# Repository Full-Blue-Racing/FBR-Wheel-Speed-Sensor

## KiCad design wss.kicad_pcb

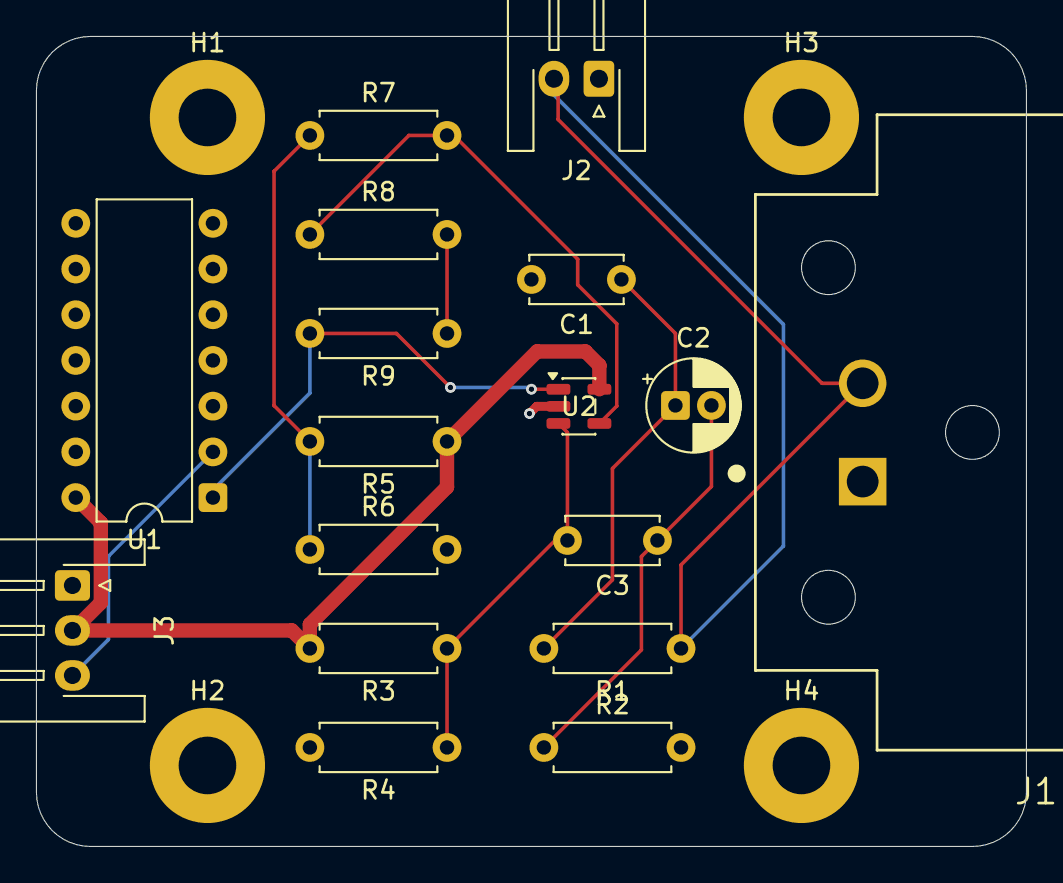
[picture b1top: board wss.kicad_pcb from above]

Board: 2 copper layers, 55.0 x 45.0 mm, 21 parts (0 on the bottom side), 11 nets.

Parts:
C1: 80n; C_Disc_D5.0mm_W2.5mm_P5.00mm
C2: 10u; CP_Radial_D5.0mm_P2.00mm
C3: 1u; C_Disc_D5.0mm_W2.5mm_P5.00mm
H1, H2, H3, H4: MountingHole_Pad; MountingHole_3.2mm_M3_Pad
J1: Conn_01x02; TE_DT13-2P
J2: Conn_01x02; JST_XH_S2B-XH-A-1_1x02_P2.50mm_Horizontal
J3: Conn_01x03; JST_XH_S3B-XH-A-1_1x03_P2.50mm_Horizontal
R1: 3.9k; R_Axial_DIN0207_L6.3mm_D2.5mm_P7.62mm_Horizontal
R2: 10k; R_Axial_DIN0207_L6.3mm_D2.5mm_P7.62mm_Horizontal
R3, R4, R5, R6: 150k; R_Axial_DIN0207_L6.3mm_D2.5mm_P7.62mm_Horizontal
R7: 5.6k; R_Axial_DIN0207_L6.3mm_D2.5mm_P7.62mm_Horizontal
R8: 5.6M; R_Axial_DIN0207_L6.3mm_D2.5mm_P7.62mm_Horizontal
R9: 0; R_Axial_DIN0207_L6.3mm_D2.5mm_P7.62mm_Horizontal
U1: 74HC14; DIP-14_W7.62mm
U2: TLV9061xDBV; SOT-23-5

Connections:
+3V3: J3.2, R3.2, R5.1, U1.14 (VCC), U2.5 (V+)
/Signal2: J1.2, J2.2, R1.1
/Signal_Output: J3.3, U1.2
GND: C1.2, H1.1, H2.1, H3.1, H4.1, J1.1, J2.1, J3.1, R2.2, R4.2, R6.2, U1.3, U1.4, U1.5, U1.6, U1.7 (GND), U1.8, U1.9, U1.10, U1.11, U1.12, U1.13, U2.2 (V-)
unnamed: C1.1, C2.1, R1.2
unnamed: C2.2, C3.1, R2.1
unnamed: R5.2, R6.1, R7.1
unnamed: R8.2, R9.1
unnamed: R9.2, U1.1, U2.1
unnamed: C3.2, R3.1, R4.1, U2.3 (+)
unnamed: R7.2, R8.1, U2.4 (-)

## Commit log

2026-04-13 Upload to GitHub
2026-04-17 Add text and labels
2026-05-01 added schmitt trigger comparator
